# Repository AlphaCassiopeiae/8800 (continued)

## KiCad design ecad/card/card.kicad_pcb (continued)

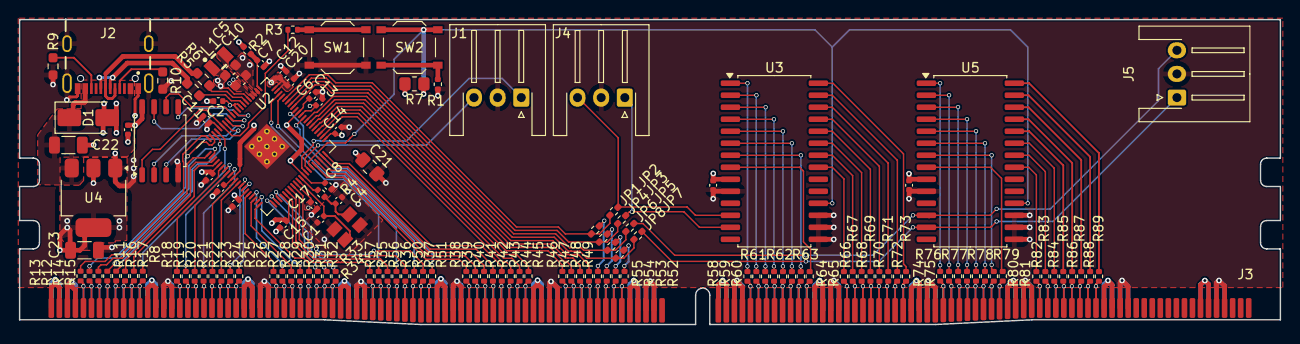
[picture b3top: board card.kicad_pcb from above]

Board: 4 copper layers, 133.4 x 32.2 mm, 136 parts (0 on the bottom side), 194 nets.

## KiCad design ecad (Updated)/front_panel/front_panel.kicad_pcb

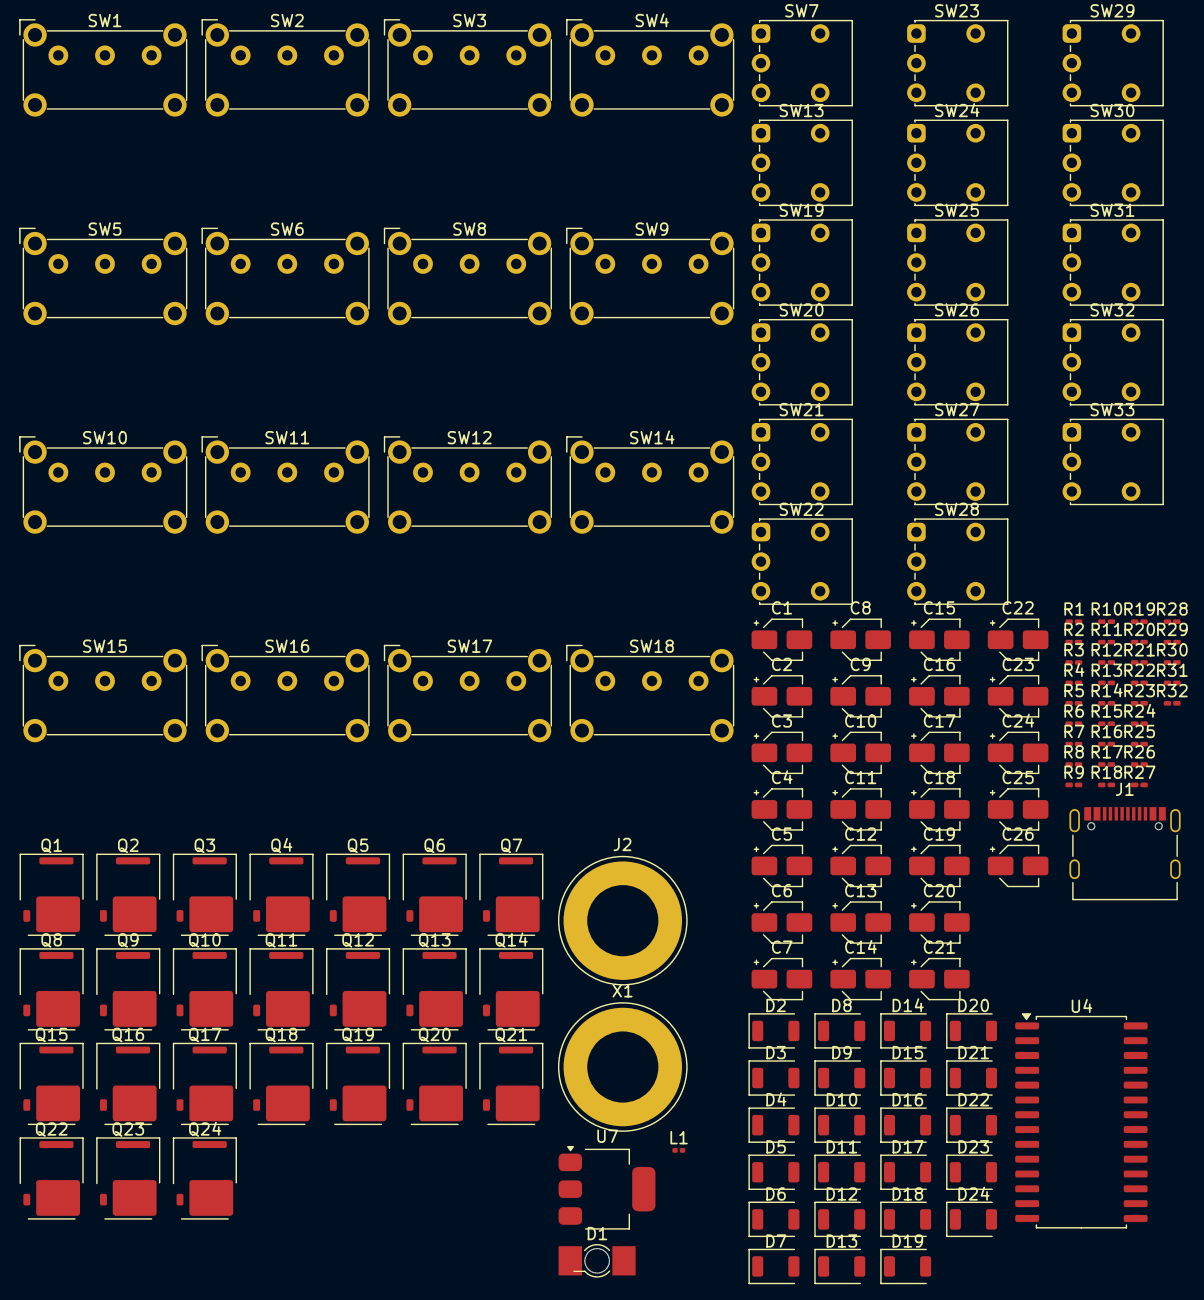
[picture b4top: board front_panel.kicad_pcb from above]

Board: 2 copper layers, 145 parts (0 on the bottom side), 65 nets, no tracks yet.

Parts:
C1, C2, C4, C5, C6, C7, C8, C9, C10, C11, C12, C13, C14, C17, C22, C23, C26: 100n; CP_Elec_3x5.4
C3, C16, C18, C19: 4.7u; CP_Elec_3x5.4
C15, C20, C21: 10u; CP_Elec_3x5.4
C24, C25: 15p; CP_Elec_3x5.4
D1: LED; LED_Osram_Lx_P47F_D2mm_ReverseMount
D2, D3, D4, D5, D6, D7, D8, D9, D10, D11, D12, D13, D14, D15, D16, D17, D18, D19, D20, D21, D22, D23, D24: LED; LED_1206_3216Metric_ReverseMount_Hole1.8x2.4mm
J1: USB_C_Receptacle_USB2.0_14P; USB_C_Receptacle_Palconn_UTC16-G
J2: Conn_01x03_Pin; Banana_Jack_1Pin
L1: 3.3u; L_0201_0603Metric
Q1, Q2, Q3, Q4, Q5, Q6, Q7, Q8, Q9, Q10, Q11, Q12, Q13, Q14, Q15, Q16, Q17, Q18, Q19, Q20, Q21, Q22, Q23, Q24: NMOS; GaN_Systems_GaNPX-3_5x6.6mm_Drain2.93x0.6mm
R1, R2, R3, R4, R5, R8, R10, R11, R13, R14, R15, R16, R19, R20, R22, R23, R25, R26, R27, R28, R29, R30, R31, R32: 220; R_0201_0603Metric_Pad0.64x0.40mm_HandSolder
R6: 33; R_0201_0603Metric_Pad0.64x0.40mm_HandSolder
R7, R9: 27; R_0201_0603Metric_Pad0.64x0.40mm_HandSolder
R12, R21, R24: 1k; R_0201_0603Metric_Pad0.64x0.40mm_HandSolder
R17, R18: 5.1k; R_0201_0603Metric_Pad0.64x0.40mm_HandSolder
SW1, SW2, SW3, SW4, SW5, SW6, SW8, SW9, SW10, SW11, SW12, SW14, SW15, SW16, SW17, SW18: SW_SPDT; SW_E-Switch_EG1224_SPDT_Angled
SW7: SPI TEST; SW_Push_1P2T_Vertical_E-Switch_800UDP8P1A1M6
SW13: FRONT PANEL TEST SWTICH; SW_Push_1P2T_Vertical_E-Switch_800UDP8P1A1M6
SW19, SW20, SW21, SW22, SW23, SW24, SW25, SW26, SW27, SW28, SW29, SW30, SW31, SW32: SW_Push; SW_Push_1P2T_Vertical_E-Switch_800UDP8P1A1M6
SW33: SW_SPDT; SW_Push_1P2T_Vertical_E-Switch_800UDP8P1A1M6
U4: MCP23017_SO; SOIC-28W_7.5x17.9mm_P1.27mm
U7: NCP1117-3.3_SOT223; SOT-223-3_TabPin2
X1: ABM8-272-T3; Banana_Jack_1Pin

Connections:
3.3V: C1.1, C17.1, C21.1, C22.1, C26.1, R1.2, R2.2, R3.2, R4.2, R5.2, R8.2, R10.2, R11.2, R13.2, R14.2, R15.2, R16.2, R19.2, R20.2, R22.2, R23.2, R25.2, R26.2, R27.2, R28.2, R29.2, R30.2, R31.2, R32.2, SW1.2 (B), SW2.2 (B), SW3.2 (B), SW4.2 (B), SW5.2 (B), SW6.2 (B), SW8.2 (B), SW9.2 (B), SW10.2 (B), SW11.2 (B), SW12.2 (B), SW14.2 (B), SW15.2 (B), SW16.2 (B), SW17.2 (B), SW18.2 (B), SW19.1, SW20.1, SW21.1, SW22.1, SW23.1, SW24.1, SW25.1, SW26.1, SW27.1, SW28.1, SW29.1, SW30.1, SW31.1, SW32.1, SW33.2 (B), U4.9 (VDD), U7.2 (VO)
+1V1: C2.1, C3.1, C4.1, C19.1, L1.1
+3V3: C5.1, C6.1, C7.1, C8.1, C9.1, C10.1, C11.1, C12.1, C13.1, C14.1, C15.1, C18.1, C23.1, R6.1
/COL1: Q1.3 (S), Q5.3 (S), Q9.3 (S), Q13.3 (S), Q17.3 (S), Q21.3 (S), U4.7 (GPB6)
/COL2: Q2.3 (S), Q6.3 (S), Q10.3 (S), Q14.3 (S), Q18.3 (S), Q22.3 (S), U4.8 (GPB7)
/COL3: Q3.3 (S), Q7.3 (S), Q11.3 (S), Q15.3 (S), Q19.3 (S), Q23.3 (S), U4.21 (GPA0)
/COL4: Q4.3 (S), Q8.3 (S), Q12.3 (S), Q16.3 (S), Q20.3 (S), Q24.3 (S), U4.22 (GPA1)
/ROW1: Q1.1 (D), Q2.1 (D), Q3.1 (D), Q4.1 (D), U4.1 (GPB0)
/ROW2: Q5.1 (D), Q6.1 (D), Q7.1 (D), Q8.1 (D), U4.2 (GPB1)
/ROW3: Q9.1 (D), Q10.1 (D), Q11.1 (D), Q12.1 (D), U4.3 (GPB2)
/ROW4: Q13.1 (D), Q14.1 (D), Q15.1 (D), Q16.1 (D), U4.4 (GPB3)
/ROW5: Q17.1 (D), Q18.1 (D), Q19.1 (D), Q20.1 (D), U4.5 (GPB4)
/ROW6: Q21.1 (D), Q22.1 (D), Q23.1 (D), Q24.1 (D), U4.6 (GPB5)
/USB_D+: J1.A6 (D+), J1.B6 (D+), R7.2
/USB_D-: J1.A7 (D-), J1.B7 (D-), R9.2
/~USB_BOOT: R12.1, SW7.2
A0: Q1.2 (G), SW1.1 (A)
A1: Q2.2 (G), SW2.1 (A)
A2: Q3.2 (G), SW3.1 (A)
A3: Q4.2 (G), SW4.1 (A)
A4: Q5.2 (G), SW5.1 (A)
A5: Q6.2 (G), SW6.1 (A)
A6: Q7.2 (G), SW8.1 (A)
A7: Q8.2 (G), SW9.1 (A)
A8: Q9.2 (G), SW10.1 (A)
A9: Q10.2 (G), SW11.1 (A)
A10: Q11.2 (G), SW12.1 (A)
A11: Q12.2 (G), SW14.1 (A)
A12: Q13.2 (G), SW15.1 (A)
A13: Q14.2 (G), SW16.1 (A)
A14: Q15.2 (G), SW17.1 (A)
A15: Q16.2 (G), SW18.1 (A)
GND: C1.2, C2.2, C3.2, C4.2, C5.2, C6.2, C7.2, C8.2, C9.2, C10.2, C11.2, C12.2, C13.2, C14.2, C15.2, C16.1, C17.2, C18.2, C19.2, C20.2, C21.2, C22.2, C23.2, C24.2, C25.1, C26.2, J1.A1 (GND), J1.A12 (GND), J1.B1 (GND), J1.B12 (GND), J1.S1 (SHIELD), R17.2, R18.2, R24.2, SW1.3 (C), SW2.3 (C), SW3.3 (C), SW4.3 (C), SW5.3 (C), SW6.3 (C), SW7.1, SW8.3 (C), SW9.3 (C), SW10.3 (C), SW11.3 (C), SW12.3 (C), SW14.3 (C), SW15.3 (C), SW16.3 (C), SW17.3 (C), SW18.3 (C), SW33.3 (C), U4.10 (VSS), U4.15 (A0), U4.16 (A1), U4.17 (A2), U7.1 (GND)
unnamed: C25.2, R21.1
unnamed: D1.2 (A), R1.1
unnamed: D2.2 (A), R2.1
unnamed: D3.2 (A), R3.1
unnamed: D4.2 (A), R4.1
unnamed: D5.2 (A), R5.1
unnamed: D6.2 (A), R8.1
unnamed: D7.2 (A), R10.1
unnamed: D8.2 (A), R11.1
unnamed: D9.2 (A), R13.1
unnamed: D10.2 (A), R14.1
unnamed: D11.2 (A), R15.1
unnamed: D12.2 (A), R16.1
unnamed: D13.2 (A), R19.1
unnamed: D14.2 (A), R20.1
unnamed: D15.2 (A), R22.1
unnamed: D16.2 (A), R23.1
unnamed: D17.2 (A), R25.1
unnamed: D18.2 (A), R26.1
unnamed: D19.2 (A), R27.1
unnamed: D20.2 (A), R28.1
unnamed: D21.2 (A), R29.1
unnamed: D22.2 (A), R30.1
unnamed: D23.2 (A), R31.1
unnamed: D24.2 (A), R32.1
unnamed: J1.A5 (CC1), R17.1
unnamed: J1.B5 (CC2), R18.1
unnamed: R24.1, SW13.1
unnamed: C16.2, R6.2
unnamed: C24.1, X1.1
ON: SW33.1 (A), U4.18 (~RESET)
VBUS: C20.1, J1.A4 (VBUS), J1.A9 (VBUS), J1.B4 (VBUS), J1.B9 (VBUS), U7.3 (VI)

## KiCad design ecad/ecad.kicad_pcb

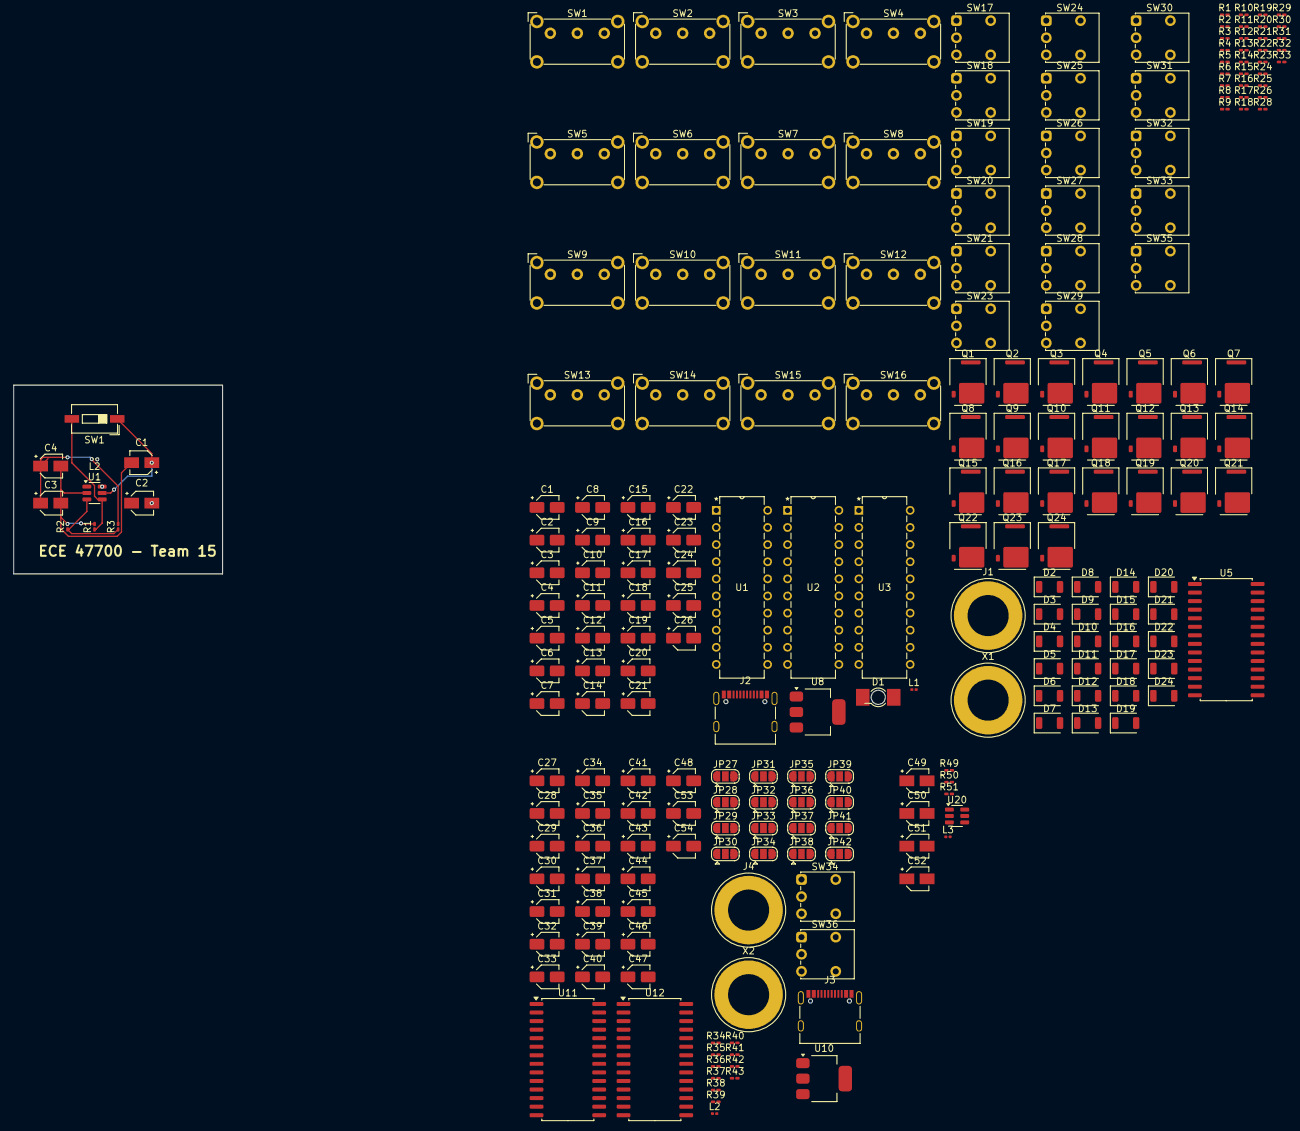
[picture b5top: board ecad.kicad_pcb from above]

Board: 4 copper layers, 226 parts (0 on the bottom side), 121 nets.

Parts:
C1, C2, C3, C4, C49, C50, C51, C52: C; CP_Elec_3x5.3
C1#2, C3#2, C4#2, C5, C6, C7, C8, C9, C10, C11, C12, C13, C17, C23, C24, C25, C26, C27, C29, C30, C31, C32, C33, C34, C35, C36, C37, C38, C39, C43, C44, C45: 100n; CP_Elec_3x5.4
C2#2, C18, C19, C20, C28, C46, C47, C48: 4.7u; CP_Elec_3x5.4
C14, C21, C22, C40, C41, C42: 10u; CP_Elec_3x5.4
C15, C16, C53, C54: 15p; CP_Elec_3x5.4
D1: LED; LED_Osram_Lx_P47F_D2mm_ReverseMount
D2, D3, D4, D5, D6, D7, D8, D9, D10, D11, D12, D13, D14, D15, D16, D17, D18, D19, D20, D21, D22, D23, D24: LED; LED_1206_3216Metric_ReverseMount_Hole1.8x2.4mm
J1, J4: Conn_01x03_Pin; Banana_Jack_1Pin
J2, J3: USB_C_Receptacle_USB2.0_14P; USB_C_Receptacle_Palconn_UTC16-G
JP27, JP28, JP29, JP30, JP31, JP32, JP33, JP34, JP35, JP36, JP37, JP38, JP39, JP40, JP41, JP42: SolderJumper_3_Open; SolderJumper-3_P1.3mm_Open_RoundedPad1.0x1.5mm
L1, L2: 3.3u; L_0201_0603Metric
L2#2, L3: L; L_0201_0603Metric
Q1, Q2, Q3, Q4, Q5, Q6, Q7, Q8, Q9, Q10, Q11, Q12, Q13, Q14, Q15, Q16, Q17, Q18, Q19, Q20, Q21, Q22, Q23, Q24: NMOS; GaN_Systems_GaNPX-3_5x6.6mm_Drain2.93x0.6mm
R1, R49: ?; R_0201_0603Metric_Pad0.64x0.40mm_HandSolder
R1#2, R2, R3#2, R4, R5, R6, R7, R8, R9, R10, R11, R12, R13, R14, R15, R16, R17, R18, R19, R20, R21, R22, R23, R24: 220; R_0201_0603Metric_Pad0.64x0.40mm_HandSolder
R2#2, R3, R50, R51: R_US; R_0201_0603Metric_Pad0.64x0.40mm_HandSolder
R25, R26, R35, R36: 27; R_0201_0603Metric_Pad0.64x0.40mm_HandSolder
R28, R29, R30, R34, R41, R42, R43: 1k; R_0201_0603Metric_Pad0.64x0.40mm_HandSolder
R31: 33; R_0201_0603Metric_Pad0.64x0.40mm_HandSolder
R32, R33, R37, R38: 5.1k; R_0201_0603Metric_Pad0.64x0.40mm_HandSolder
R39, R40: 100k; R_0201_0603Metric_Pad0.64x0.40mm_HandSolder
SW1: SW_SPST; SW_DIP_SPSTx01_Slide_6.7x4.1mm_W6.73mm_P2.54mm_LowProfile_J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
SW1#2, SW2, SW3, SW4, SW5, SW6, SW7, SW8, SW9, SW10, SW11, SW12, SW13, SW14, SW15, SW16: SW_SPDT; SW_E-Switch_EG1224_SPDT_Angled
SW17, SW18, SW19, SW20, SW21, SW23, SW24, SW25, SW26, SW27, SW28, SW29, SW30, SW31, SW34, SW36: SW_Push; SW_Push_1P2T_Vertical_E-Switch_800UDP8P1A1M6
SW32: SW_SPDT; SW_Push_1P2T_Vertical_E-Switch_800UDP8P1A1M6
SW33: SPI TEST; SW_Push_1P2T_Vertical_E-Switch_800UDP8P1A1M6
SW35: FRONT PANEL TEST SWTICH; SW_Push_1P2T_Vertical_E-Switch_800UDP8P1A1M6
U1, U20: MCP16331x-xCH; SOT-23-6
U1#2, U2, U3: TLC59211IN; N20
U5, U11, U12: MCP23017_SO; SOIC-28W_7.5x17.9mm_P1.27mm
U8, U10: NCP1117-3.3_SOT223; SOT-223-3_TabPin2
X1, X2: ABM8-272-T3; Banana_Jack_1Pin

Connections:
3.3V: C22.1, C23.1, C24.1, C25.1, C26.1, C47.1, R1#2.2, R2.2, R3#2.2, R4.2, R5.2, R6.2, R7.2, R8.2, R9.2, R10.2, R11.2, R12.2, R13.2, R14.2, R15.2, R16.2, R17.2, R18.2, R19.2, R20.2, R21.2, R22.2, R23.2, R24.2, R34.1, SW1#2.2 (B), SW2.2 (B), SW3.2 (B), SW4.2 (B), SW5.2 (B), SW6.2 (B), SW7.2 (B), SW8.2 (B), SW9.2 (B), SW10.2 (B), SW11.2 (B), SW12.2 (B), SW13.2 (B), SW14.2 (B), SW15.2 (B), SW16.2 (B), SW17.1, SW18.1, SW19.1, SW20.1, SW21.1, SW23.1, SW24.1, SW25.1, SW26.1, SW27.1, SW28.1, SW29.1, SW30.1, SW31.1, SW32.2 (B), U1#2.20 (VCC), U2.20 (VCC), U3.20 (VCC), U5.9 (VDD), U8.2 (VO)
+1V1: C1#2.1, C2#2.1, C3#2.1, C19.1, C27.1, C28.1, C29.1, C46.1, L1.1, L2.1
+3V3: C4#2.1, C5.1, C6.1, C7.1, C8.1, C9.1, C10.1, C11.1, C12.1, C13.1, C14.1, C17.1, C20.1, C30.1, C31.1, C32.1, C33.1, C34.1, C35.1, C36.1, C37.1, C38.1, C39.1, C40.1, C42.1, C43.1, C44.1, C45.1, R31.1, R39.1, R40.1, U10.2 (VO), U11.9 (VDD), U12.9 (VDD)
+5V: C1.1, C51.1, R49.1, SW1.1 (A), U1.5 (V_{IN}), U20.4 (EN), U20.5 (V_{IN})
/A0_LED: D1.1 (K), U1#2.19 (*Y1)
/A1_LED: D2.1 (K), U1#2.18 (*Y2)
/A2_LED: D3.1 (K), U1#2.17 (*Y3)
/A3_LED: D4.1 (K), U1#2.16 (*Y4)
/A4_LED: D5.1 (K), U1#2.15 (*Y5)
/A5_LED: D6.1 (K), U1#2.14 (*Y6)
/A6_LED: D7.1 (K), U1#2.13 (*Y7)
/A7_LED: D8.1 (K), U1#2.12 (*Y8)
/A8_LED: D9.1 (K), U2.19 (*Y1)
/A9_LED: D10.1 (K), U2.18 (*Y2)
/A10_LED: D11.1 (K), U2.17 (*Y3)
/A11_LED: D12.1 (K), U2.16 (*Y4)
/A12_LED: D13.1 (K), U2.15 (*Y5)
/A13_LED: D14.1 (K), U2.14 (*Y6)
/A14_LED: D15.1 (K), U2.13 (*Y7)
/A15_LED: D16.1 (K), U2.12 (*Y8)
/COL1: Q1.3 (S), Q5.3 (S), Q9.3 (S), Q13.3 (S), Q17.3 (S), Q21.3 (S), U5.7 (GPB6)
/COL2: Q2.3 (S), Q6.3 (S), Q10.3 (S), Q14.3 (S), Q18.3 (S), Q22.3 (S), U5.8 (GPB7)
/COL3: Q3.3 (S), Q7.3 (S), Q11.3 (S), Q15.3 (S), Q19.3 (S), Q23.3 (S), U5.21 (GPA0)
/COL4: Q4.3 (S), Q8.3 (S), Q12.3 (S), Q16.3 (S), Q20.3 (S), Q24.3 (S), U5.22 (GPA1)
/D0_LED: D17.1 (K), U3.19 (*Y1)
/D1_LED: D18.1 (K), U3.18 (*Y2)
/D2_LED: D19.1 (K), U3.17 (*Y3)
/D3_LED: D20.1 (K), U3.16 (*Y4)
/D4_LED: D21.1 (K), U3.15 (*Y5)
/D5_LED: D22.1 (K), U3.14 (*Y6)
/D6_LED: D23.1 (K), U3.13 (*Y7)
/D7_LED: D24.1 (K), U3.12 (*Y8)
/Generic_Card/I2C0_SCL: JP28.3 (B), U11.12 (SCK)
/Generic_Card/I2C0_SDA: JP27.3 (B), U11.13 (SDA)
/Generic_Card/I2C1_SCL: JP30.3 (B), U12.12 (SCK)
/Generic_Card/I2C1_SDA: JP29.3 (B), U12.13 (SDA)
/Generic_Card/USB_D+: J3.A6 (D+), J3.B6 (D+), R35.2
/Generic_Card/USB_D-: J3.A7 (D-), J3.B7 (D-), R36.2
/Generic_Card/~RESET: R39.2, R40.2, SW36.2, U11.18 (~RESET), U12.18 (~RESET)
/Generic_Card/~USB_BOOT: R43.1, SW34.2
/ROW1: Q1.1 (D), Q2.1 (D), Q3.1 (D), Q4.1 (D), U5.1 (GPB0)
/ROW2: Q5.1 (D), Q6.1 (D), Q7.1 (D), Q8.1 (D), U5.2 (GPB1)
/ROW3: Q9.1 (D), Q10.1 (D), Q11.1 (D), Q12.1 (D), U5.3 (GPB2)
/ROW4: Q13.1 (D), Q14.1 (D), Q15.1 (D), Q16.1 (D), U5.4 (GPB3)
/ROW5: Q17.1 (D), Q18.1 (D), Q19.1 (D), Q20.1 (D), U5.5 (GPB4)
/ROW6: Q21.1 (D), Q22.1 (D), Q23.1 (D), Q24.1 (D), U5.6 (GPB5)
/USB_D+: J2.A6 (D+), J2.B6 (D+), R25.2
/USB_D-: J2.A7 (D-), J2.B7 (D-), R26.2
/~USB_BOOT: R30.1, SW33.2
A0: Q1.2 (G), SW1#2.1 (A), U1#2.2 (D1)
A1: Q2.2 (G), SW2.1 (A), U1#2.3 (D2)
A2: Q3.2 (G), SW3.1 (A), U1#2.4 (D3)
A3: Q4.2 (G), SW4.1 (A), U1#2.5 (D4)
A4: Q5.2 (G), SW5.1 (A), U1#2.6 (D5)
A5: Q6.2 (G), SW6.1 (A), U1#2.7 (D6)
A6: Q7.2 (G), SW7.1 (A), U1#2.8 (D7)
A7: Q8.2 (G), SW8.1 (A), U1#2.9 (D8)
A8: Q9.2 (G), SW9.1 (A), U2.2 (D1)
A9: Q10.2 (G), SW10.1 (A), U2.3 (D2)
A10: Q11.2 (G), SW11.1 (A), U2.4 (D3)
A11: Q12.2 (G), SW12.1 (A), U2.5 (D4)
A12: Q13.2 (G), SW13.1 (A), U2.6 (D5)
A13: Q14.2 (G), SW14.1 (A), U2.7 (D6)
A14: Q15.2 (G), SW15.1 (A), U2.8 (D7)
A15: Q16.2 (G), SW16.1 (A), U2.9 (D8)
D0: Q17.2 (G), U3.2 (D1)
D1: Q18.2 (G), U3.3 (D2)
D2: Q19.2 (G), U3.4 (D3)
D3: Q20.2 (G), U3.5 (D4)
D4: Q21.2 (G), U3.6 (D5)
D5: Q22.2 (G), U3.7 (D6)
D6: Q23.2 (G), U3.8 (D7)
D7: Q24.2 (G), U3.9 (D8)
GND: C1.2, C1#2.2, C2#2.2, C3.2, C3#2.2, C4.2, C4#2.2, C5.2, C6.2, C7.2, C8.2, C9.2, C10.2, C11.2, C12.2, C13.2, C14.2, C15.1, C16.2, C17.2, C18.1, C19.2, C20.2, C21.2, C22.2, C23.2, C24.2, C25.2, C26.2, C27.2, C28.2, C29.2, C30.2, C31.2, C32.2, C33.2, C34.2, C35.2, C36.2, C37.2, C38.2, C39.2, C40.2, C41.2, C42.2, C43.2, C44.2, C45.2, C46.2, C47.2, C48.2, C49.2, C51.2, C52.2, C53.1, C54.2, J2.A1 (GND), J2.A12 (GND), J2.B1 (GND), J2.B12 (GND), J2.S1 (SHIELD), J3.A1 (GND), J3.A12 (GND), J3.B1 (GND), J3.B12 (GND), J3.S1 (SHIELD), R1.2, R2#2.2, R28.2, R32.2, R33.2, R37.2, R38.2, R42.1, R49.2, R50.2, SW1#2.3 (C), SW2.3 (C), SW3.3 (C), SW4.3 (C), SW5.3 (C), SW6.3 (C), SW7.3 (C), SW8.3 (C), SW9.3 (C), SW10.3 (C), SW11.3 (C), SW12.3 (C), SW13.3 (C), SW14.3 (C), SW15.3 (C), SW16.3 (C), SW32.3 (C), SW33.1, SW34.1, U1.2 (GND), U1#2.11 (GND), U2.11 (GND), U3.11 (GND), U5.10 (VSS), U5.15 (A0), U5.16 (A1), U5.17 (A2), U8.1 (GND), U10.1 (GND), U11.10 (VSS), U11.15 (A0), U11.16 (A1), U11.17 (A2), U12.10 (VSS), U12.15 (A0), U12.16 (A1), U12.17 (A2), U20.2 (GND)
unnamed: C3.1, C4.1, L2#2.2, R3.2
unnamed: C15.2, R29.1
unnamed: C49.1, C52.1, L3.2, R51.2
unnamed: C53.2, R41.1
unnamed: D1.2 (A), R1#2.1
unnamed: D2.2 (A), R2.1
unnamed: D3.2 (A), R3#2.1
unnamed: D4.2 (A), R4.1
unnamed: D5.2 (A), R5.1
unnamed: D6.2 (A), R6.1
unnamed: D7.2 (A), R7.1
unnamed: D8.2 (A), R8.1
unnamed: D9.2 (A), R9.1
unnamed: D10.2 (A), R10.1
unnamed: D11.2 (A), R11.1
unnamed: D12.2 (A), R12.1
unnamed: D13.2 (A), R13.1
unnamed: D14.2 (A), R14.1
unnamed: D15.2 (A), R15.1
unnamed: D16.2 (A), R16.1
unnamed: D17.2 (A), R17.1
unnamed: D18.2 (A), R18.1
unnamed: D19.2 (A), R19.1
unnamed: D20.2 (A), R20.1
unnamed: D21.2 (A), R21.1
unnamed: D22.2 (A), R22.1
unnamed: D23.2 (A), R23.1
unnamed: D24.2 (A), R24.1
unnamed: J2.A5 (CC1), R32.1
unnamed: J2.B5 (CC2), R33.1
unnamed: J3.A5 (CC1), R38.1
unnamed: J3.B5 (CC2), R37.1
unnamed: R28.1, SW35.1
unnamed: R42.2, SW36.1
unnamed: R1.1, SW1.2 (B), U1.4 (EN)
unnamed: C2.1, U1.1 (BOOST)
unnamed: C2.2, L2#2.1, U1.6 (SW)
unnamed: R2#2.1, R3.1, U1.3 (V_{FB})
unnamed: C18.2, R31.2
unnamed: C16.1, X1.1
unnamed: C48.1, R34.2
unnamed: C54.1, X2.1
unnamed: C50.1, U20.1 (BOOST)
unnamed: C50.2, L3.1, U20.6 (SW)
unnamed: R50.1, R51.1, U20.3 (V_{FB})
ON: SW32.1 (A), U5.18 (~RESET)
VBUS: C21.1, C41.1, J2.A4 (VBUS), J2.A9 (VBUS), J2.B4 (VBUS), J2.B9 (VBUS), J3.A4 (VBUS), J3.A9 (VBUS), J3.B4 (VBUS), J3.B9 (VBUS), U8.3 (VI), U10.3 (VI)

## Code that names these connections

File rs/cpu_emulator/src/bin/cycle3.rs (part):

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        
        "out pins, 16",       // Output address to pins
        
        "wait 1 gpio 4",      // Wait for XRDY high
        
        "in pins, 8",         // Read 8-bit data from pins
        "push block",         // Push data to RX FIFO
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    pio: &mut Common<'a, PIO0>, 
    sm: &mut StateMachine<'a, PIO0, 2>,
    data_addr_pins: &[&Pin<'a, PIO0>],
    mwrt_pin: &Pin<'a, PIO0>,
) {
    // PIO program for address output, data output, and MWRT# control
    let prg = pio_asm!(
        ".wrap_target",

        "set pins, 1",        // Deassert MWRT# (inactive high)

        // set all data addr pins to output
        "pull block",
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        "pull block",         // Get address from TX FIFO
        "out pins, 24",       // Output address to pins

        "set pins, 0",        // Assert MWRT# (active low)

        "wait 1 gpio 4",      // Wait for XRDY high (write complete)
        "irq 2",              // notify write complete

        // set data to input and addr to output
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    let mut cfg = PioConfig::default();
    cfg.use_program(&pio.load_program(&prg.program), &[]);
    cfg.set_out_pins(data_addr_pins);
    cfg.set_set_pins(&[mwrt_pin]);
    cfg.clock_divider = (U56F8!(125_000_000) / 20 / 200).to_fixed(); // 100kHz operation
    cfg.shift_out.auto_fill = false;
    cfg.shift_out.direction = ShiftDirection::Right;
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    sm.set_config(&cfg);

    // set swrite pin as output
    sm.set_pin_dirs(embassy_rp::pio::Direction::Out, &[mwrt_pin]);
}

#[embassy_executor::main]
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    let p = embassy_rp::init(Default::default());

    let mut rst = Input::new(p.PIN_3, Pull::Up);
    let mut prdy = Input::new(p.PIN_2, Pull::Down);
    let mut hlta = Output::new(p.PIN_36, Level::Low);
    let mut panel = Output::new(p.PIN_1, Level::High); // low active

    // Create PIO state machines
    let Pio { mut common, mut irq1, mut irq2, mut sm1, mut sm2, .. } = Pio::new(p.PIO0, Irqs);
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    // Take slice of data pins (D7-D0)
    let data_pins = &data_addr_pins[0..8];

    // Setup pin for SMEMR# control and xrdy
    let smemr_pin = &pio1.common.make_pio_pin(p.PIN_34);  // SMEMR# pin (output, active low)
    common.make_pio_pin(p.PIN_4); // XRDY pin (input, active high)
    let mwrt_pin = &common.make_pio_pin(p.PIN_6); // active low


    // Configure PIO state machines
    setup_smemr(&mut pio1.common, &mut pio1.sm0, smemr_pin);
    setup_reads(&mut common, &mut sm1, &addr_pins, &data_pins);
    
    setup_writes(&mut common, &mut sm2, &data_addr_pins, mwrt_pin);


    // Enable state machines
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
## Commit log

2025-01-27 Setup KiCAD project
2025-01-27 rs workspace .gitignore
2025-01-27 Changed EDA file
2025-01-29 Worked on Power PCB
2025-01-29 To add front panel
2025-01-31 Started Front Panel
2025-02-10 ooga booga
2025-02-10 Added files
2025-02-12 initial card schematic
2025-02-12 shit pico code that doesn't work
2025-02-19 lib additions
2025-02-19 reorder pages
2025-02-24 Front Panel Schematic Done
    Finished Part of the Schematic, need to check for ERC.
2025-02-24 recall basic r/w functionality
2025-02-24 add runner and wavedrom
2025-02-24 need HAL stuff added to recall
2025-02-24 New Project Layout
2025-02-25 PCB Update
2025-02-26 New labels
2025-02-26 Testing Resets Placed
2025-02-26 Push
2025-02-26 new card boxes
2025-02-26 Front Panel Done, Time for ERC
2025-02-26 Ready for Layout
2025-02-26 library ecad changes
2025-02-26 Back Plane Nearly Complete
2025-02-26 WOW CODE embassy
2025-02-26 library ecad USB-C
2025-02-26 Added 3 new project files
2025-02-26 pull
2025-02-26 New Component Library
2025-02-26 drop-in kingbright
2025-02-27 recall should flash
2025-02-27 emulator progress (runner/recall)
2025-02-27 Finished Library
2025-02-27 Changes not in last push
2025-02-28 timing info pg 1
2025-03-03 KiCAD 8.0 symbol and footprint library
2025-03-04 Additional projects
2025-03-04 setup relative library tables
2025-03-04 relative to KIPRJMOD
2025-03-04 pin libraries
2025-03-05 fixup card schematic new lib
2025-03-05 Realigned numbers
2025-03-05 boxed out card
2025-03-05 Added Connectors
2025-03-05 fixup card labels
2025-03-05 integrate edge card symbol into card
2025-03-05 update diagrams
2025-03-05 Finish Front Panel
2025-03-05 card layout, lib updates
2025-03-05 initial card layout
2025-03-05 fix zone priorities
2025-03-05 finish backplane beta
2025-03-05 Front Panel Layout
2025-03-10 PCB Changes
2025-03-10 Update PCB
2025-03-10 near-final card layout
2025-03-11 resolve some card DRC
2025-03-11 card setup missing 3D
2025-03-11 card add UART output, protection diode
2025-03-11 misc power via fixes
2025-03-11 fixup unconnects card
2025-03-12 smaller button
2025-03-12 change
2025-03-12 various changes
2025-03-12 more panel layout changes
2025-03-12 fix backplane pins
2025-03-12 Finished Card and Panel Schematics
2025-03-12 recall builds
2025-03-12 add back panel switch and tram outline
2025-03-13 more backplane. add nathan's panel changes
2025-03-13 remap changes, various card panel fixes
2025-03-13 add prices and digikey links to parts
2025-03-13 near-final panel routing
2025-03-13 add panel pins table
2025-03-13 minor panel adj.
2025-03-13 backplane with addr
2025-03-13 backplane with different bus names
2025-03-13 panel, routing, USB, switches, LDO
2025-03-14 panel silkscreen
2025-03-14 Back panel changes
2025-03-14 add labels on card
2025-03-14 more panel work
2025-03-14 new diode, some panel pwr routing
2025-03-14 Backplane changes
2025-03-14 Back Panel Done
2025-03-14 Panel final? route
2025-03-14 card connector, diode changes
2025-03-14 card silkscreen
2025-03-14 Datasheets done
2025-03-14 general team number silkscreen
2025-03-14 KiCADstepup
2025-03-14 rotate card UART 90
2025-03-14 Gerber Files
2025-03-14 Card gerbers
2025-03-14 Front panel gerbers
2025-03-14 add LCSC reverse LED
2025-03-14 BOM change
2025-03-14 Panel Changes
2025-03-14 new LCSC library components
2025-03-14 Card BOM
2025-03-14 current production try
2025-03-14 save panel
2025-03-14 clean up ecad die
2025-03-14 clean up ecad
2025-03-14 revisions after feedback
2025-03-14 fixup H excludes rules
2025-03-14 backplane add debug vias
2025-03-14 Fixed File Structure
2025-03-15 various production cost changes
2025-03-15 archive all again
2025-03-15 ecad no weird resistor group
2025-03-15 Schematics
2025-03-15 I/O Changes
2025-03-15 Swap GND (1) and 3.3V (3)
2025-03-16 production
2025-03-16 new panel routing
2025-03-16 stackup changes, prodction
2025-03-16 clean up backplane a bit
2025-03-16 update arhives
2025-03-17 double up for HASL
2025-03-17 backplane reverse FFC wiring
2025-03-17 minor backplane revisions
2025-03-17 change card HASL finish definition
2025-03-17 new ecad archives
2025-03-17 add vishay LED symbol footprints for comparison
2025-03-17 fixup panel io expansion pinout
2025-03-17 production fixups
2025-03-17 additional production fixups
2025-03-17 clean up archives
2025-03-17 add Affinity file for silkscreen design
2025-03-18 Files for JLCPCB
2025-03-19 increase via sizes
2025-03-19 minor routing adj.
2025-03-20 minor panel routing changes
2025-03-20 enlarge holes to 0.3mm
2025-03-26 framwork for tram communication (lib.rs)
2025-03-26 cleaner tramsim framework
2025-03-26 i2x interchange done
2025-03-27 tram-recall interface
2025-03-28 updated bus assignments
2025-03-29 inerchange progress
2025-04-07 trying to clean up framework
2025-04-09 recall builds, main function needs work
2025-04-09 runner framework
2025-04-09 vendor tcl rpi openocd
2025-04-09 vendor tcl rpi openocd target
2025-04-09 tram all lcds, interchange i2c to leds, and update toolchain
2025-04-10 arm-none-eabi-gdb rpi openocd cortex-m toolchain
2025-04-11 Changes on remapping for archives
2025-04-15 still working on runner
2025-04-15 yay interchange
2025-04-15 fix rust analyzer complaints
2025-04-16 Laser Silkscreen
2025-04-16 CAD Stuff IDK
2025-04-17 yayy
2025-04-18 CAD Stuff
2025-04-22 added cpu simulation
2025-04-22 cpu emulator builds, no GPIO
2025-04-22 bus reads work
2025-04-22 reads with proper pins on real hardware
2025-04-22 CAD + Silkscreen Stuff
2025-04-23 reads work on 2
2025-04-23 writes working
2025-04-23 KiCad + CAD
2025-04-24 ready to test cpu_em
2025-04-24 build issues resolved
2025-04-24 starting interchange main loop
2025-04-24 bus reads work on pin 34
2025-04-24 interchange buttons working
2025-04-24 reads and writes done
2025-04-25 some cpu emluator
2025-04-25 reset works over bus
2025-04-25 errors need fixing
2025-04-25 add more test vals
2025-04-25 integrated
2025-04-25 no errors integration cpu memory
2025-04-25 oooo
2025-04-25 new ram implementation
2025-04-25 clean up emulator files
2025-04-25 basic test program
2025-04-26 final emu + interchange (deposit not ready yet)
2025-04-28 better instruction execution
2025-04-28 cleanup ram
2025-04-28 cleanup ram 2
2025-04-28 deposit works
2025-04-29 not there
2025-04-29 deposit perfect
2025-04-30 examine and next buttons work
2025-04-30 poster assets
